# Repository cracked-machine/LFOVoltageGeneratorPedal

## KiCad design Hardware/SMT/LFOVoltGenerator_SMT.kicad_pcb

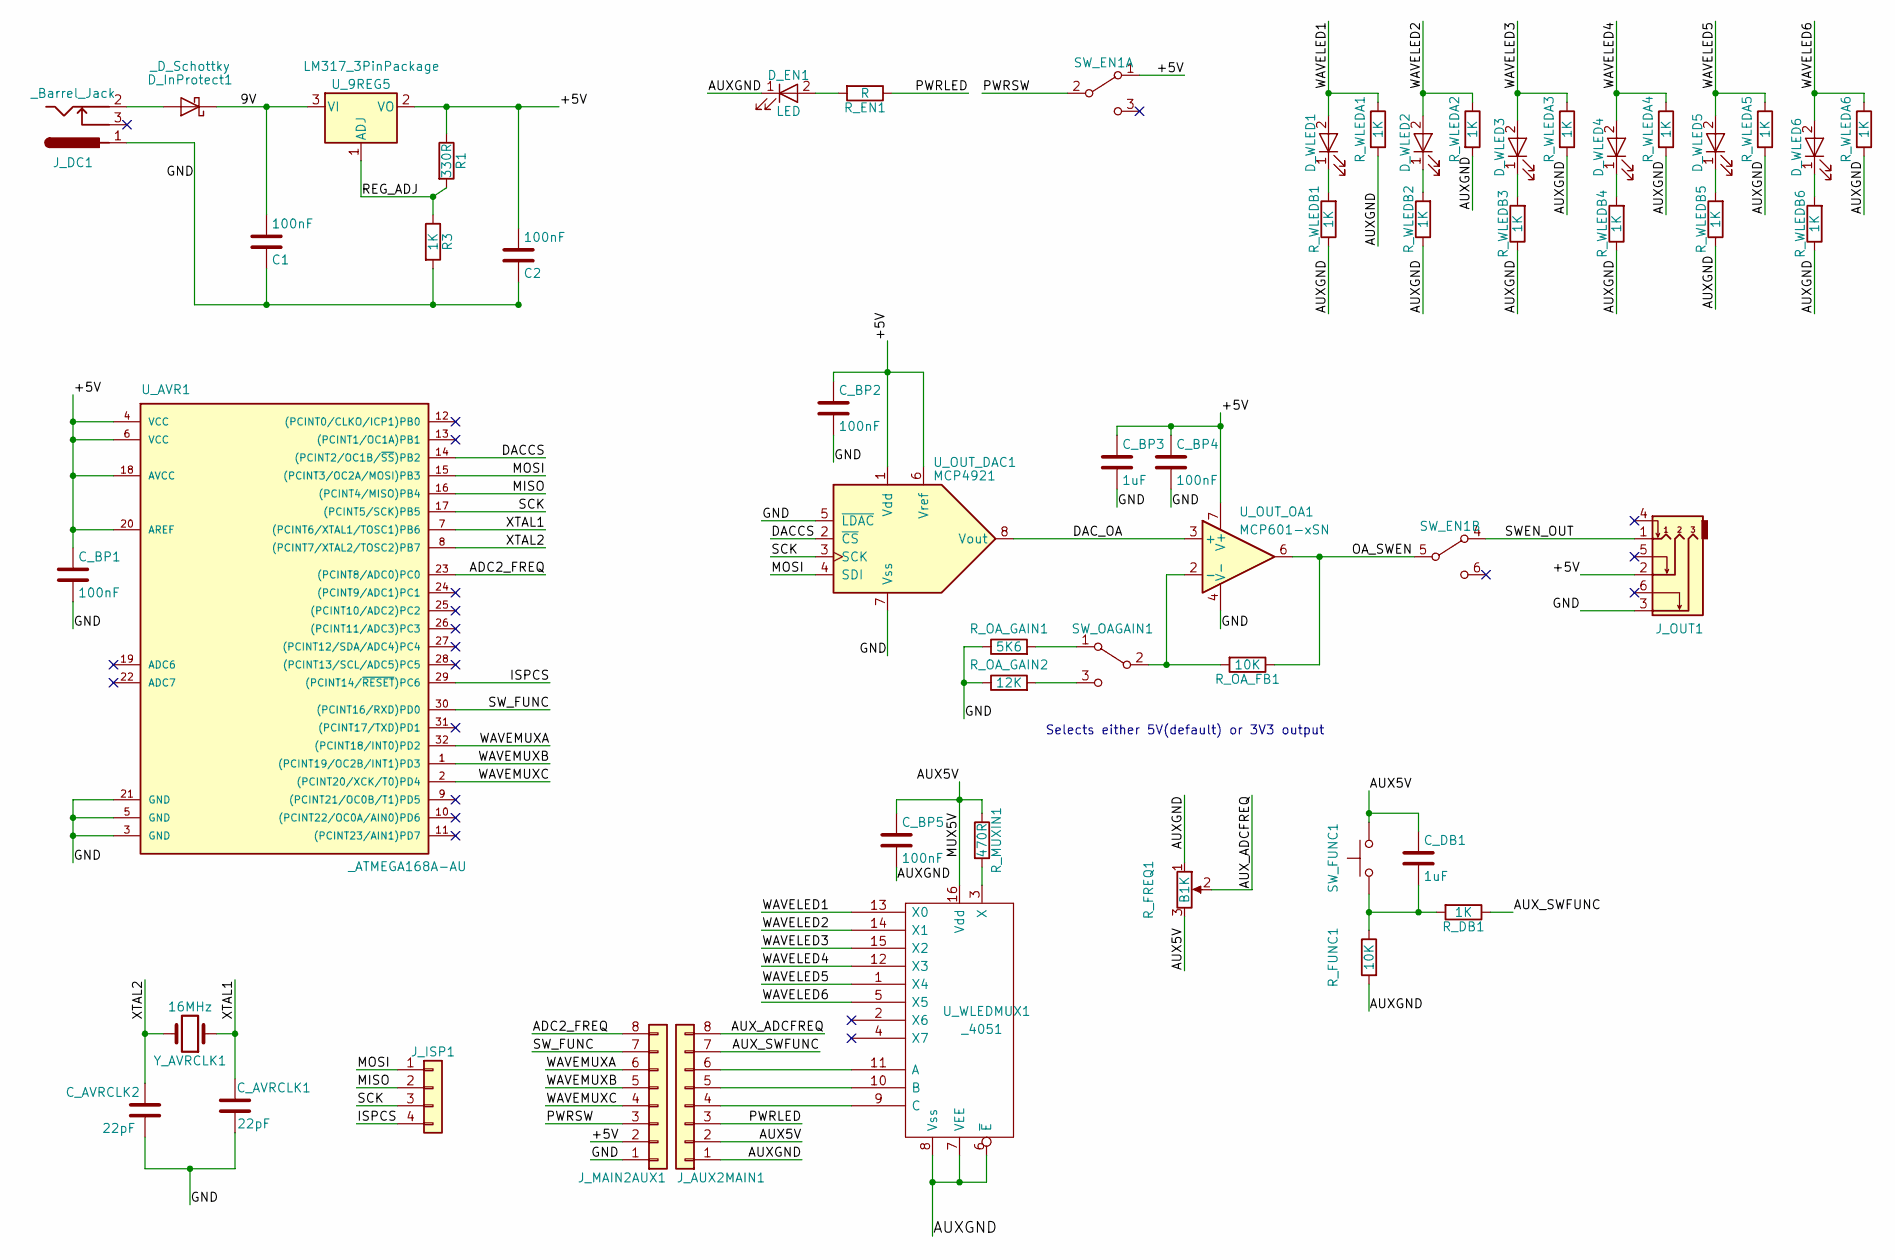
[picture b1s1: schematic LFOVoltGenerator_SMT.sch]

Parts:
C1, C2: 100nF; C_0805_HandSoldering
C_AVRCLK1, C_AVRCLK2: 22pF; C_0805_HandSoldering
C_BP1, C_BP2, C_BP4, C_BP5: 100nF; C_0805_HandSoldering
C_BP3: 1uF; C_0805_HandSoldering
C_DB1: 1uF; C_0805_HandSoldering
D_EN1: LED; LED_0805_HandSoldering
D_InProtect1: _D_Schottky; D_SOD-123
D_WLED1, D_WLED2, D_WLED3, D_WLED4, D_WLED5, D_WLED6: LED; LED_0805_HandSoldering
J_AUX2MAIN1: Conn_01x08; Pin_Header_Straight_1x08_Pitch2.54mm
J_DC1: _Barrel_Jack; BARREL_JACK
J_ISP1: Conn_01x04; Pin_Header_Straight_1x04_Pitch2.54mm
J_MAIN2AUX1: Conn_01x08; Pin_Header_Straight_1x08_Pitch2.54mm
J_OUT1: Audio-Jack-3_3Switches; TRS635mmJack
R1: 330R; R_0805_HandSoldering
R3: 1K; R_0805_HandSoldering
R_DB1: 1K; R_0805_HandSoldering
R_EN1: R; R_0805_HandSoldering
R_FREQ1: B1K; Potentiometer_Bourns_PTV09A-1_Horizontal
R_FUNC1: 10K; R_0805_HandSoldering
R_MUXIN1: 470R; R_0805_HandSoldering
R_OA_FB1: 10K; R_0805_HandSoldering
R_OA_GAIN1: 5K6; R_0805_HandSoldering
R_OA_GAIN2: 12K; R_0805_HandSoldering
R_WLEDA1, R_WLEDA2, R_WLEDA3, R_WLEDA4, R_WLEDA5, R_WLEDA6: 1K; R_0805_HandSoldering
R_WLEDB1, R_WLEDB2, R_WLEDB3, R_WLEDB4, R_WLEDB5, R_WLEDB6: 1K; R_0805_HandSoldering
SW_EN1: SW_DPDT_x2; DPDT_FOOT_ONON_ALPHA_W13MM_D12MM_P5.08MM
SW_FUNC1: SW_Push; SW_PUSH_6mm_h5mm
SW_OAGAIN1: SW_SPDT; C&K_8_6mm_SPDT_ONON
U_9REG5: LM317_3PinPackage; SOT-223-3_TabPin2
U_AVR1: _ATMEGA168A-AU; TQFP-32_7x7mm_Pitch0.8mm
U_OUT_DAC1: MCP4921; SOIC-8_3.9x4.9mm_Pitch1.27mm
U_OUT_OA1: MCP601-xSN; SOIC-8_3.9x4.9mm_Pitch1.27mm
U_WLEDMUX1: _4051; SOIC-16_3.9x9.9mm_Pitch1.27mm
Y_AVRCLK1: 16MHz; Crystal_HC49-4H_Vertical

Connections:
/9V: C1.2, D_InProtect1.1 (K), U_9REG5.3 (VI)
/+5V: C2.2, C_BP1.1, C_BP2.1, C_BP3.1, C_BP4.1, J_MAIN2AUX1.2, J_OUT1.2, R1.1, SW_EN1.1 (A), U_9REG5.2 (VO), U_AVR1.4 (VCC), U_AVR1.6 (VCC), U_AVR1.18 (AVCC), U_AVR1.20 (AREF), U_OUT_DAC1.1 (Vdd), U_OUT_DAC1.6 (Vref), U_OUT_OA1.7 (V+)
/ADC2_FREQ: J_MAIN2AUX1.8, U_AVR1.23 ((PCINT8/ADC0)PC0)
/AUX5V: C_BP5.1, C_DB1.1, J_AUX2MAIN1.2, R_FREQ1.3, R_MUXIN1.1, SW_FUNC1.1, U_WLEDMUX1.16 (Vdd)
/AUXGND: C_BP5.2, D_EN1.1 (K), J_AUX2MAIN1.1, R_FREQ1.1, R_FUNC1.2, R_WLEDA1.2, R_WLEDA2.2, R_WLEDA3.2, R_WLEDA4.2, R_WLEDA5.2, R_WLEDA6.2, R_WLEDB1.1, R_WLEDB2.1, R_WLEDB3.1, R_WLEDB4.1, R_WLEDB5.1, R_WLEDB6.1, U_WLEDMUX1.6 (~E), U_WLEDMUX1.7 (VEE), U_WLEDMUX1.8 (Vss)
/AUX_ADCFREQ: J_AUX2MAIN1.8, R_FREQ1.2
/AUX_SWFUNC: J_AUX2MAIN1.7, R_DB1.1
/DACCS: U_AVR1.14 ((PCINT2/OC1B/~SS~)PB2), U_OUT_DAC1.2 (~CS)
/DAC_OA: U_OUT_DAC1.8 (Vout), U_OUT_OA1.3 (+)
/GND: C1.1, C2.1, C_AVRCLK1.1, C_AVRCLK2.1, C_BP1.2, C_BP2.2, C_BP3.2, C_BP4.2, J_DC1.1, J_MAIN2AUX1.1, J_OUT1.3, R3.2, R_OA_GAIN1.1, R_OA_GAIN2.1, U_AVR1.3 (GND), U_AVR1.5 (GND), U_AVR1.21 (GND), U_OUT_DAC1.5 (~LDAC), U_OUT_DAC1.7 (Vss), U_OUT_OA1.4 (V-)
/ISPCS: J_ISP1.4, U_AVR1.29 ((PCINT14/~RESET~)PC6)
/MISO: J_ISP1.2, U_AVR1.16 ((PCINT4/MISO)PB4)
/MOSI: J_ISP1.1, U_AVR1.15 ((PCINT3/OC2A/MOSI)PB3), U_OUT_DAC1.4 (SDI)
/OA_SWEN: R_OA_FB1.1, SW_EN1.5 (B), U_OUT_OA1.6
/PWRLED: J_AUX2MAIN1.3, R_EN1.1
/PWRSW: J_MAIN2AUX1.3, SW_EN1.2 (B)
/REG_ADJ: R1.2, R3.1, U_9REG5.1 (ADJ)
/SCK: J_ISP1.3, U_AVR1.17 ((PCINT5/SCK)PB5), U_OUT_DAC1.3 (SCK)
/SWEN_OUT: J_OUT1.1, SW_EN1.4 (A)
/SW_FUNC: J_MAIN2AUX1.7, U_AVR1.30 ((PCINT16/RXD)PD0)
/WAVELED1: D_WLED1.2 (A), R_WLEDA1.1, U_WLEDMUX1.13 (X0)
/WAVELED2: D_WLED2.2 (A), R_WLEDA2.1, U_WLEDMUX1.14 (X1)
/WAVELED3: D_WLED3.2 (A), R_WLEDA3.1, U_WLEDMUX1.15 (X2)
/WAVELED4: D_WLED4.2 (A), R_WLEDA4.1, U_WLEDMUX1.12 (X3)
/WAVELED5: D_WLED5.2 (A), R_WLEDA5.1, U_WLEDMUX1.1 (X4)
/WAVELED6: D_WLED6.2 (A), R_WLEDA6.1, U_WLEDMUX1.5 (X5)
/WAVEMUXA: J_MAIN2AUX1.6, U_AVR1.32 ((PCINT18/INT0)PD2)
/WAVEMUXB: J_MAIN2AUX1.5, U_AVR1.1 ((PCINT19/OC2B/INT1)PD3)
/WAVEMUXC: J_MAIN2AUX1.4, U_AVR1.2 ((PCINT20/XCK/T0)PD4)
/XTAL1: C_AVRCLK1.2, U_AVR1.7 ((PCINT6/XTAL1/TOSC1)PB6), Y_AVRCLK1.1
/XTAL2: C_AVRCLK2.2, U_AVR1.8 ((PCINT7/XTAL2/TOSC2)PB7), Y_AVRCLK1.2
unnamed: C_DB1.2, R_DB1.2, R_FUNC1.1, SW_FUNC1.2
unnamed: D_EN1.2 (A), R_EN1.2
unnamed: D_InProtect1.2 (A), J_DC1.2
unnamed: D_WLED1.1 (K), R_WLEDB1.2
unnamed: D_WLED2.1 (K), R_WLEDB2.2
unnamed: D_WLED3.1 (K), R_WLEDB3.2
unnamed: D_WLED4.1 (K), R_WLEDB4.2
unnamed: D_WLED5.1 (K), R_WLEDB5.2
unnamed: D_WLED6.1 (K), R_WLEDB6.2
unnamed: J_AUX2MAIN1.4, U_WLEDMUX1.9 (C)
unnamed: J_AUX2MAIN1.5, U_WLEDMUX1.10 (B)
unnamed: J_AUX2MAIN1.6, U_WLEDMUX1.11 (A)
unnamed: R_MUXIN1.2, U_WLEDMUX1.3 (X)
unnamed: R_OA_FB1.2, SW_OAGAIN1.2 (B), U_OUT_OA1.2 (-)
unnamed: R_OA_GAIN1.2, SW_OAGAIN1.1 (A)
unnamed: R_OA_GAIN2.2, SW_OAGAIN1.3 (C)

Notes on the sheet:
Selects either 5V(default) or 3V3 output

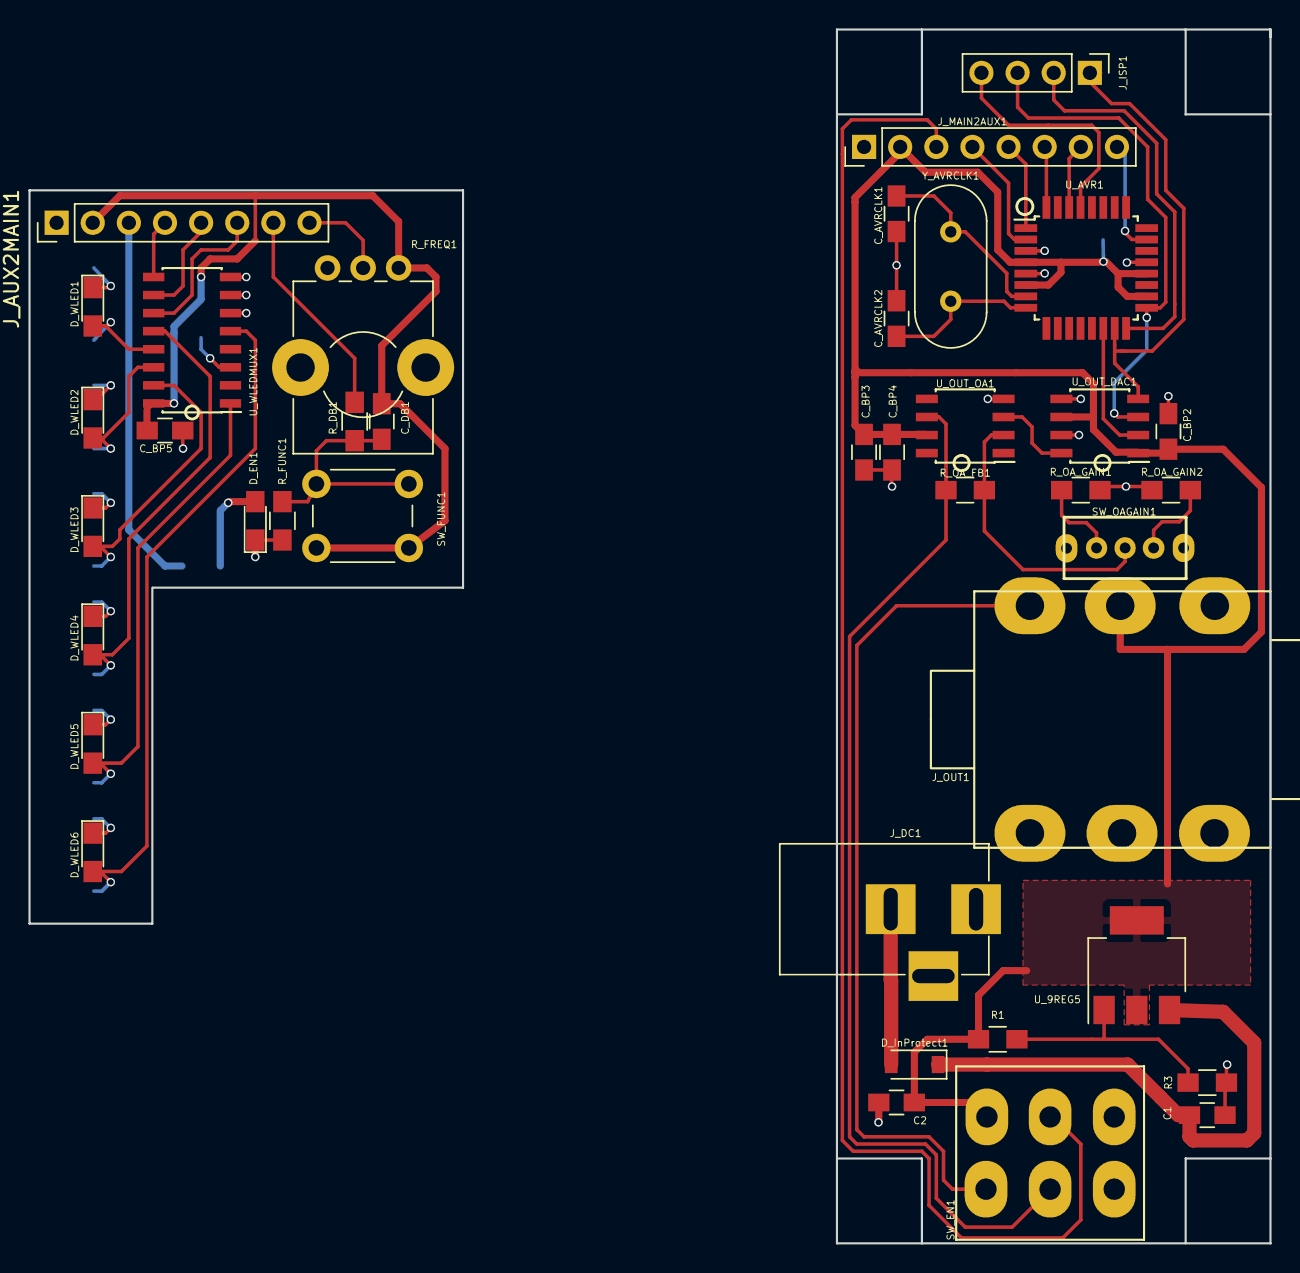
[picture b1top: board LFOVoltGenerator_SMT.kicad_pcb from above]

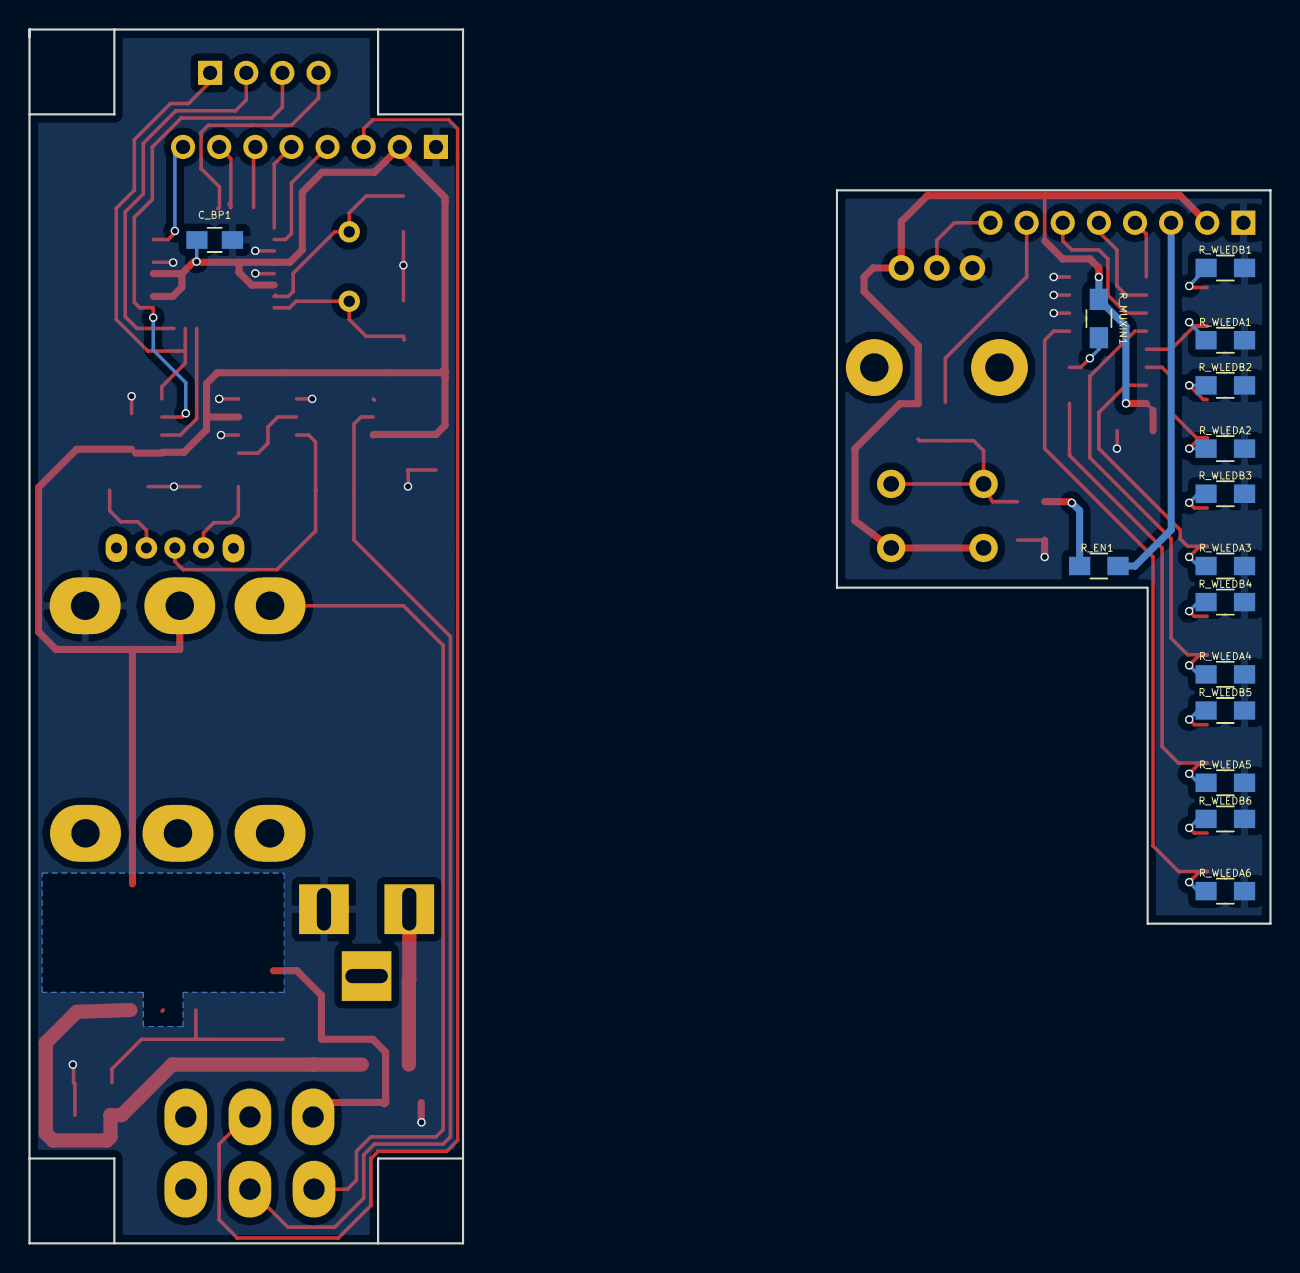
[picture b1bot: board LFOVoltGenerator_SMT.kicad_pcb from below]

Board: 2 copper layers, 87.2 x 85.3 mm, 54 parts (15 on the bottom side), 47 nets.

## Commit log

2018-03-10 correction
